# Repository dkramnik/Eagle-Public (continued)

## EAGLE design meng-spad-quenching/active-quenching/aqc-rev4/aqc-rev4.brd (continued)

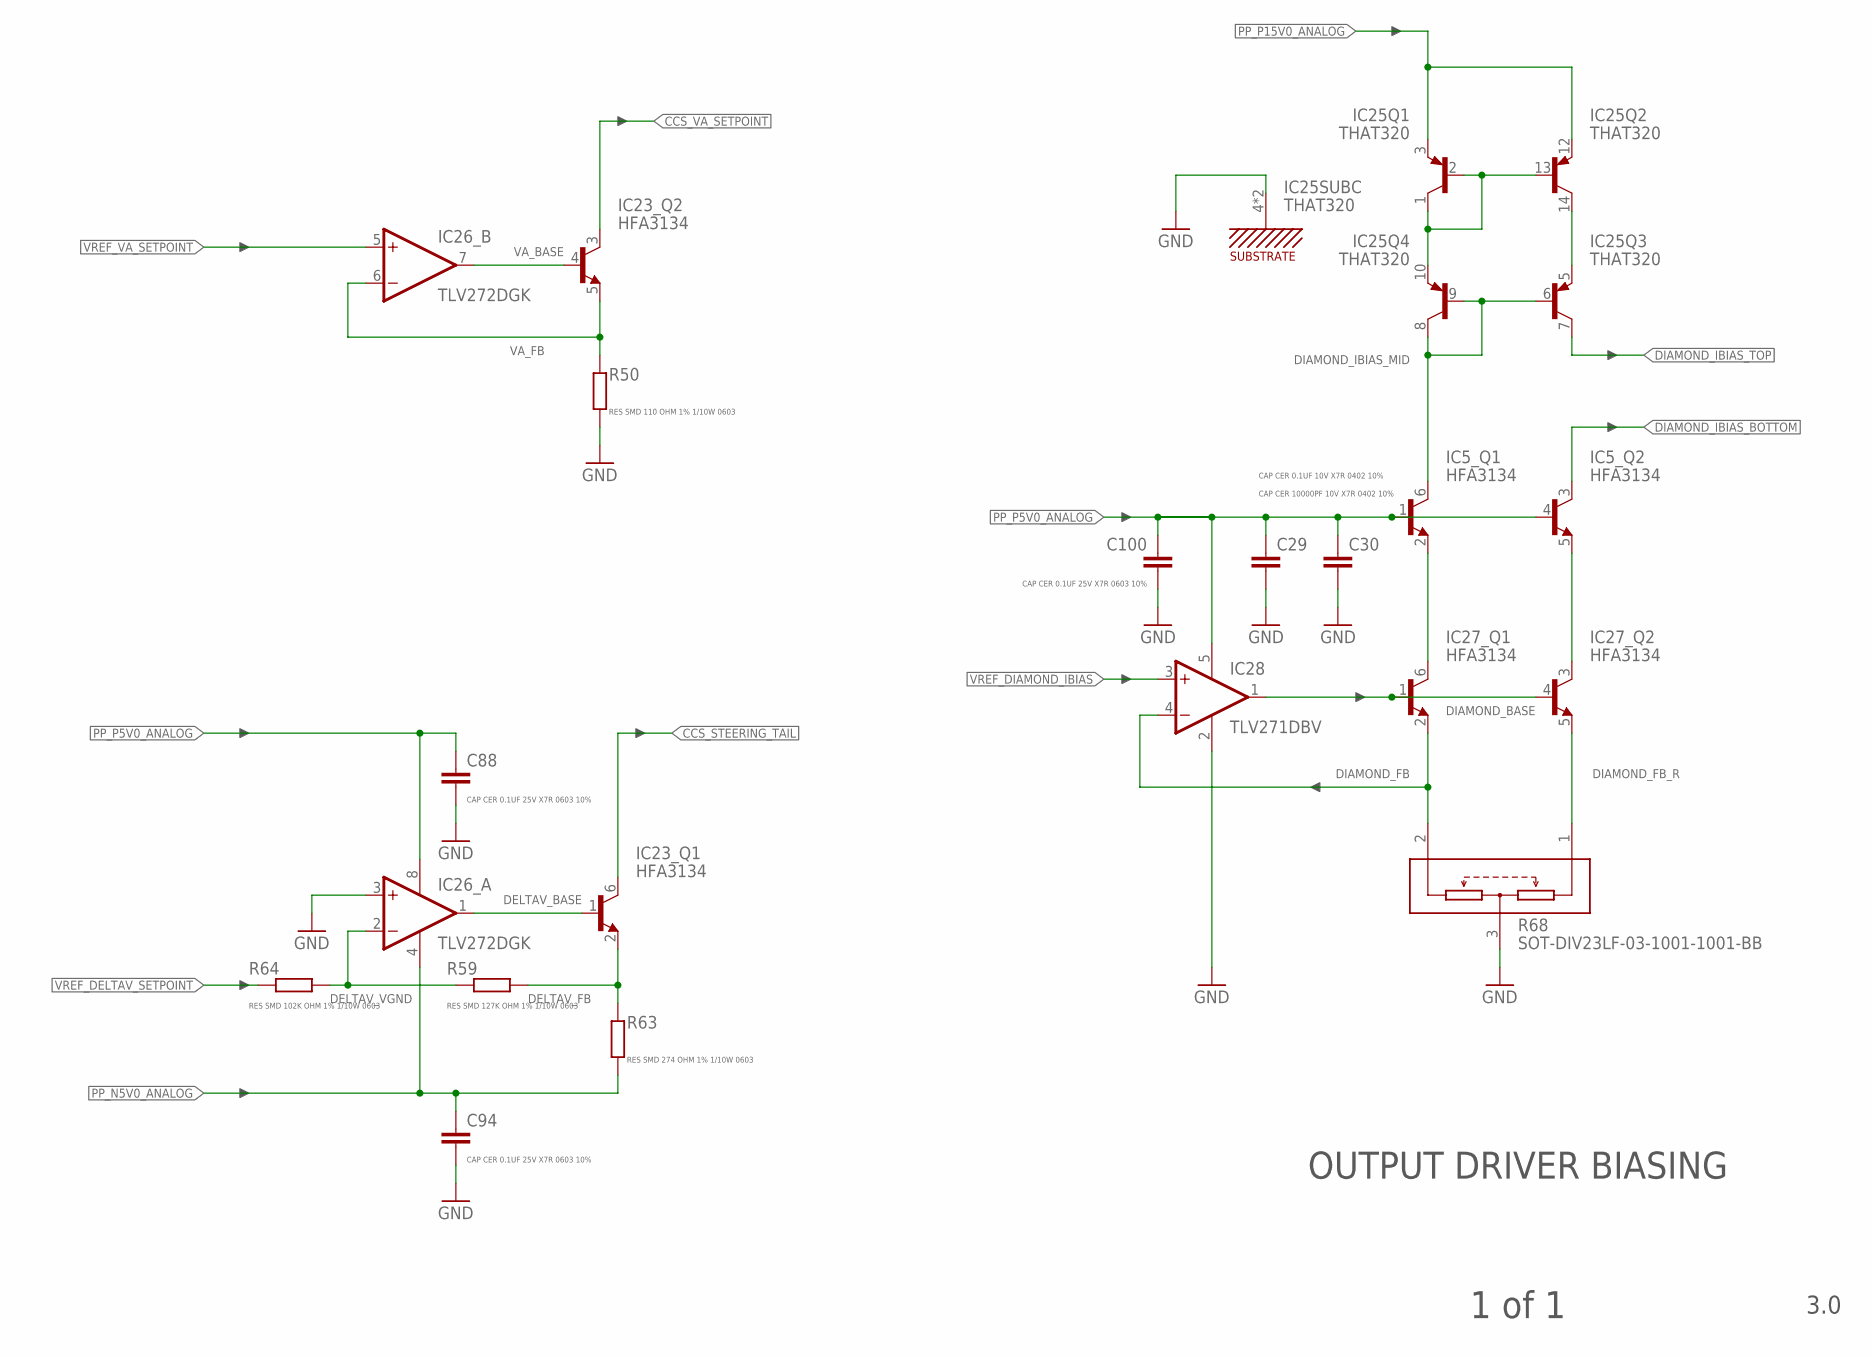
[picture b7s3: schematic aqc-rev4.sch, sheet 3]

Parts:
C29: CAP CER 0.1UF 10V X7R 0402 10%; C0402
C30: CAP CER 10000PF 10V X7R 0402 10%; C0402
C88, C94, C100: CAP CER 0.1UF 25V X7R 0603 10%; C0603
IC5, IC23, IC27: HFA3134; SOT23-6L
IC25: THAT320; SO14
IC26: TLV272DGK; MSOP8
IC28: TLV271DBV; SOT23-5
R50: RES SMD 110 OHM 1% 1/10W 0603; R0603
R59: RES SMD 127K OHM 1% 1/10W 0603; R0603
R63: RES SMD 274 OHM 1% 1/10W 0603; R0603
R64: RES SMD 102K OHM 1% 1/10W 0603; R0603
R68: SOT-DIV23LF-03-1001-1001-BB; SOT23C

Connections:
CCS_STEERING_TAIL: IC23.6 (C); also elsewhere on the board
CCS_VA_SETPOINT: IC23.3 (C); also elsewhere on the board
DELTAV_BASE: IC23.1 (B), IC26.1 (OUT)
DELTAV_FB: IC23.2 (E), R59.1, R63.2
DELTAV_VGND: IC26.2 (-IN), R59.2, R64.1
DIAMOND_BASE: IC27.1 (B), IC27.4 (B), IC28.1 (OUT)
DIAMOND_FB: IC27.2 (E), IC28.4 (-IN), R68.2 (TOP)
DIAMOND_FB_R: IC27.5 (E), R68.1 (BOTTOM)
DIAMOND_IBIAS_BOTTOM: IC5.3 (C); also elsewhere on the board
DIAMOND_IBIAS_MID: IC5.6 (C), IC25.6 (B), IC25.8 (C), IC25.9 (B)
DIAMOND_IBIAS_TOP: IC25.7 (C); also elsewhere on the board
GND: C29.2, C30.2, C88.2, C94.2, C100.2, IC25.4 (SUBC), IC25.11 (SUBC), IC26.3 (+IN), IC28.2 (V-), R50.1, R68.3 (MIDDLE); also elsewhere on the board
unnamed: IC5.2 (E), IC27.6 (C)
unnamed: IC5.5 (E), IC27.3 (C)
unnamed: IC25.1 (C), IC25.2 (B), IC25.10 (E), IC25.13 (B)
unnamed: IC25.5 (E), IC25.14 (C)
PP_N5V0_ANALOG: C94.1, IC26.4 (V-), R63.1; also elsewhere on the board
PP_P5V0_ANALOG: C29.1, C30.1, C88.1, C100.1, IC5.1 (B), IC5.4 (B), IC26.8 (V+), IC28.5 (V+); also elsewhere on the board
PP_P15V0_ANALOG: IC25.3 (E), IC25.12 (E); also elsewhere on the board
VA_BASE: IC23.4 (B), IC26.7 (OUT)
VA_FB: IC23.5 (E), IC26.6 (-IN), R50.2
VREF_DELTAV_SETPOINT: R64.2; also elsewhere on the board
VREF_DIAMOND_IBIAS: IC28.3 (+IN); also elsewhere on the board
VREF_VA_SETPOINT: IC26.5 (+IN); also elsewhere on the board

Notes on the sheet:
OUTPUT DRIVER BIASING
3.0
1 of 1

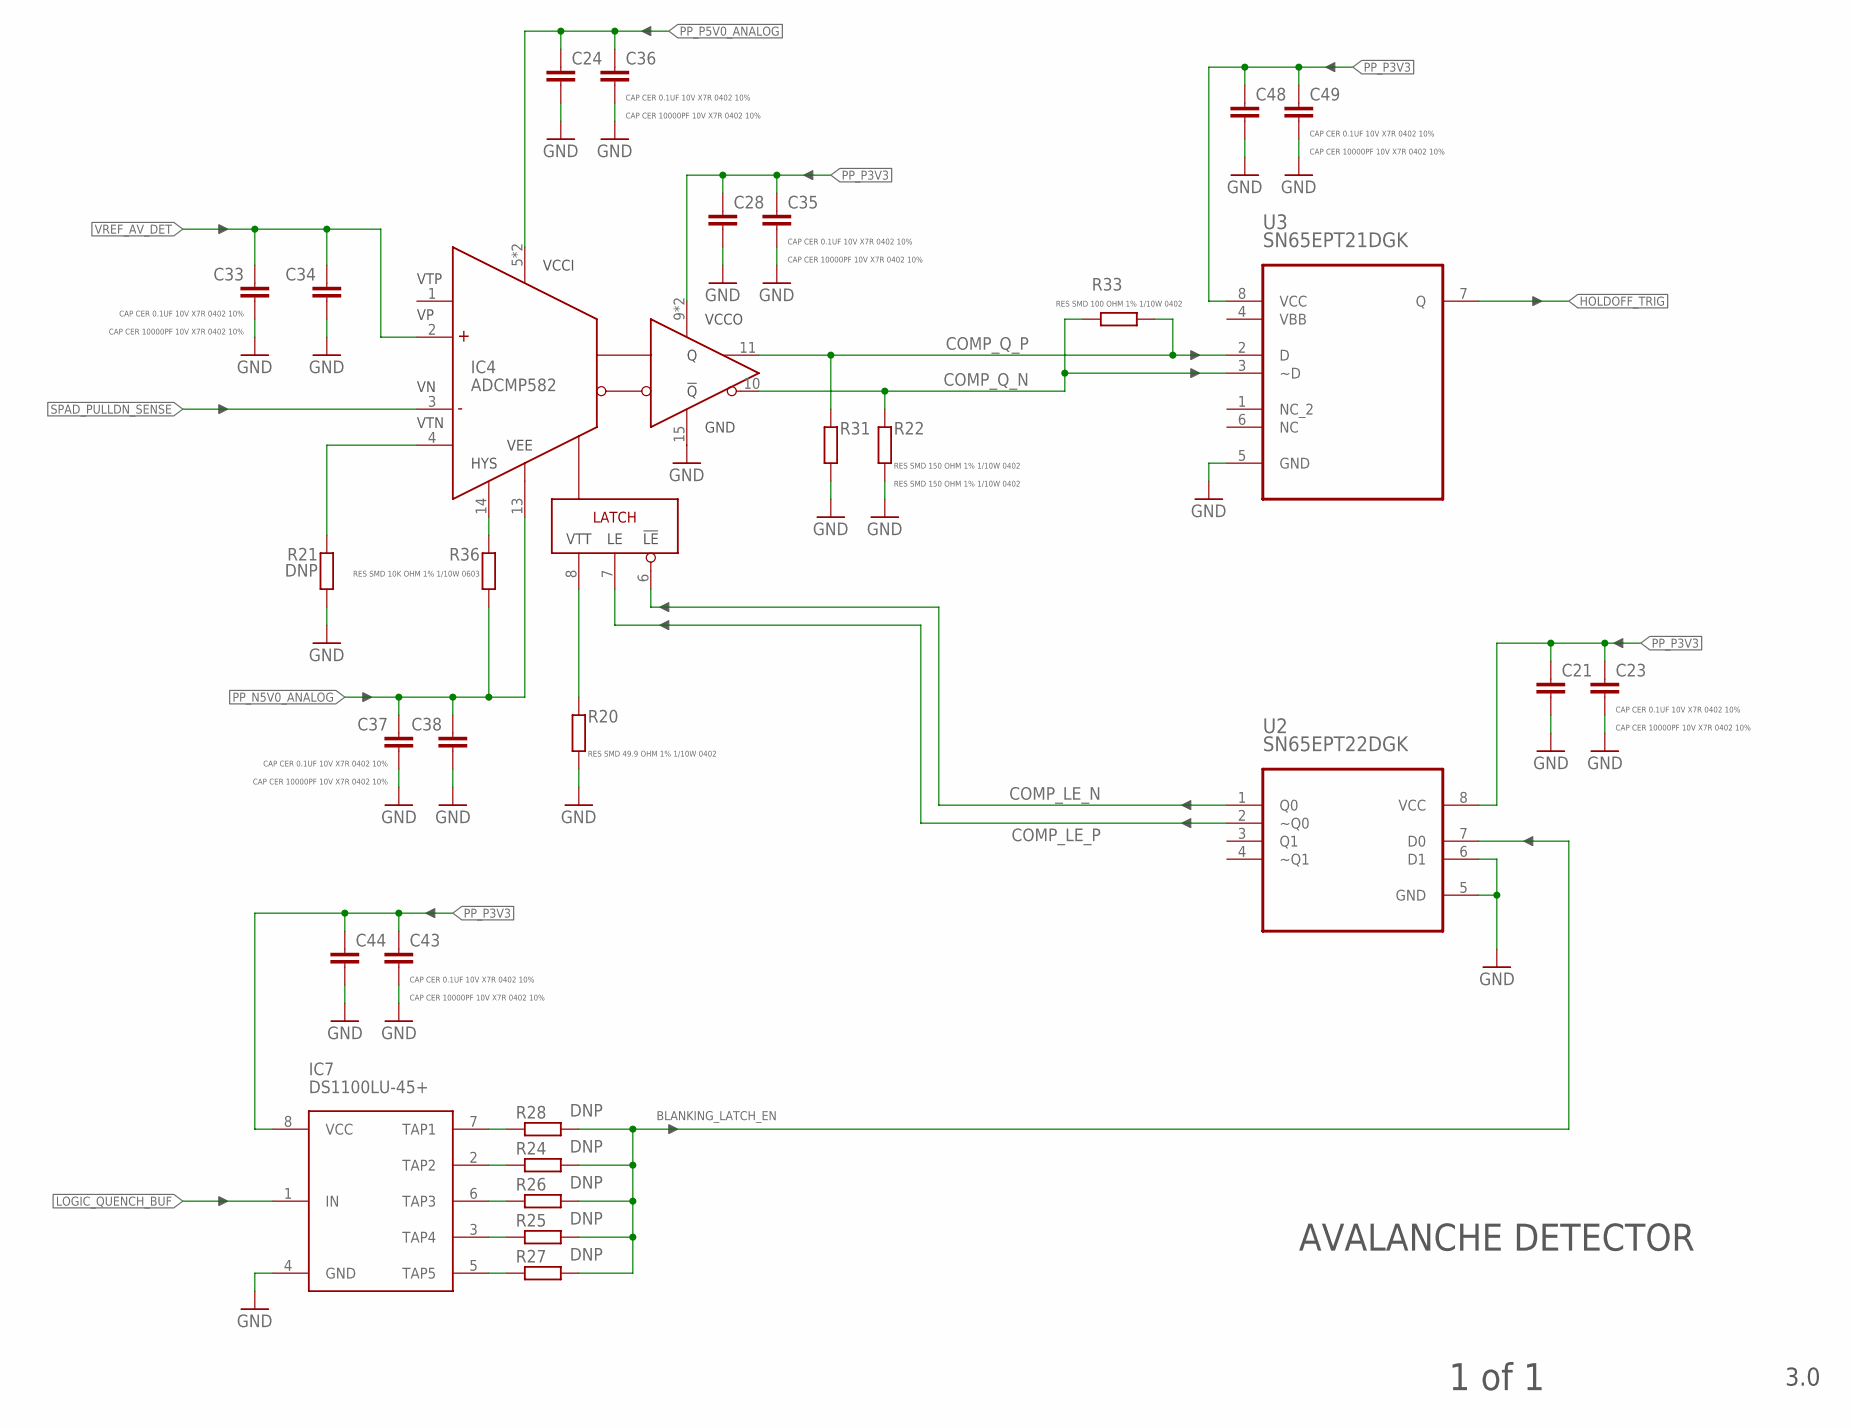
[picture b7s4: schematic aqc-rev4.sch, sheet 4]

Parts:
C21, C24, C28, C34, C38, C44, C48: CAP CER 10000PF 10V X7R 0402 10%; C0402
C23, C33, C35, C36, C37, C43, C49: CAP CER 0.1UF 10V X7R 0402 10%; C0402
IC4: ADCMP582; QFN50P300X300X80-16N
IC7: DS1100LU-45+; MSOP8
R20: RES SMD 49.9 OHM 1% 1/10W 0402; R0402
R21, R24, R25, R26, R27, R28: DNP; R0603
R22, R31: RES SMD 150 OHM 1% 1/10W 0402; R0402
R33: RES SMD 100 OHM 1% 1/10W 0402; R0402
R36: RES SMD 10K OHM 1% 1/10W 0603; R0603
U2: SN65EPT22DGK; SOP65P490X110-8N
U3: SN65EPT21DGK; SOP65P490X110-8N

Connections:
BLANKING_LATCH_EN: R24.1, R25.1, R26.1, R27.1, R28.1, U2.7 (D0)
COMP_HYS: IC4.14 (HYS), R36.2
COMP_LE_N: IC4.6 (!LE), U2.1 (Q0)
COMP_LE_P: IC4.7 (LE), U2.2 (~Q0)
COMP_Q_N: IC4.10 (!Q), R22.1, R33.1, U3.3 (~D)
COMP_Q_P: IC4.11 (Q), R31.1, R33.2, U3.2 (D)
COMP_VTN: IC4.4 (VTN), R21.2
COMP_VTT: IC4.8 (VTT), R20.1
GND: C21.2, C23.2, C24.2, C28.2, C33.2, C34.2, C35.2, C36.2, C37.2, C38.2, C43.2, C44.2, C48.2, C49.2, IC4.15 (GND), IC7.4 (GND), R20.2, R21.1, R22.2, R31.2, U2.5 (GND), U2.6 (D1), U3.5 (GND); also elsewhere on the board
HOLDOFF_TRIG: U3.7 (Q); also elsewhere on the board
LOGIC_QUENCH_BUF: IC7.1 (IN); also elsewhere on the board
PP_N5V0_ANALOG: C37.1, C38.1, IC4.13 (VEE), R36.1; also elsewhere on the board
PP_P3V3: C21.1, C23.1, C28.1, C35.1, C43.1, C44.1, C48.1, C49.1, IC4.9 (VCCO), IC4.12 (VCCO), IC7.8 (VCC), U2.8 (VCC), U3.8 (VCC); also elsewhere on the board
PP_P5V0_ANALOG: C24.1, C36.1, IC4.5 (VCCI), IC4.16 (VCCI); also elsewhere on the board
SPAD_PULLDN_SENSE: IC4.3 (VN); also elsewhere on the board
TAP1: IC7.7 (TAP1), R28.2
TAP2: IC7.2 (TAP2), R24.2
TAP3: IC7.6 (TAP3), R26.2
TAP4: IC7.3 (TAP4), R25.2
TAP5: IC7.5 (TAP5), R27.2
VBB: U3.4 (VBB)
VREF_AV_DET: C33.1, C34.1, IC4.2 (VP); also elsewhere on the board

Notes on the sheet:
AVALANCHE DETECTOR
3.0
1 of 1

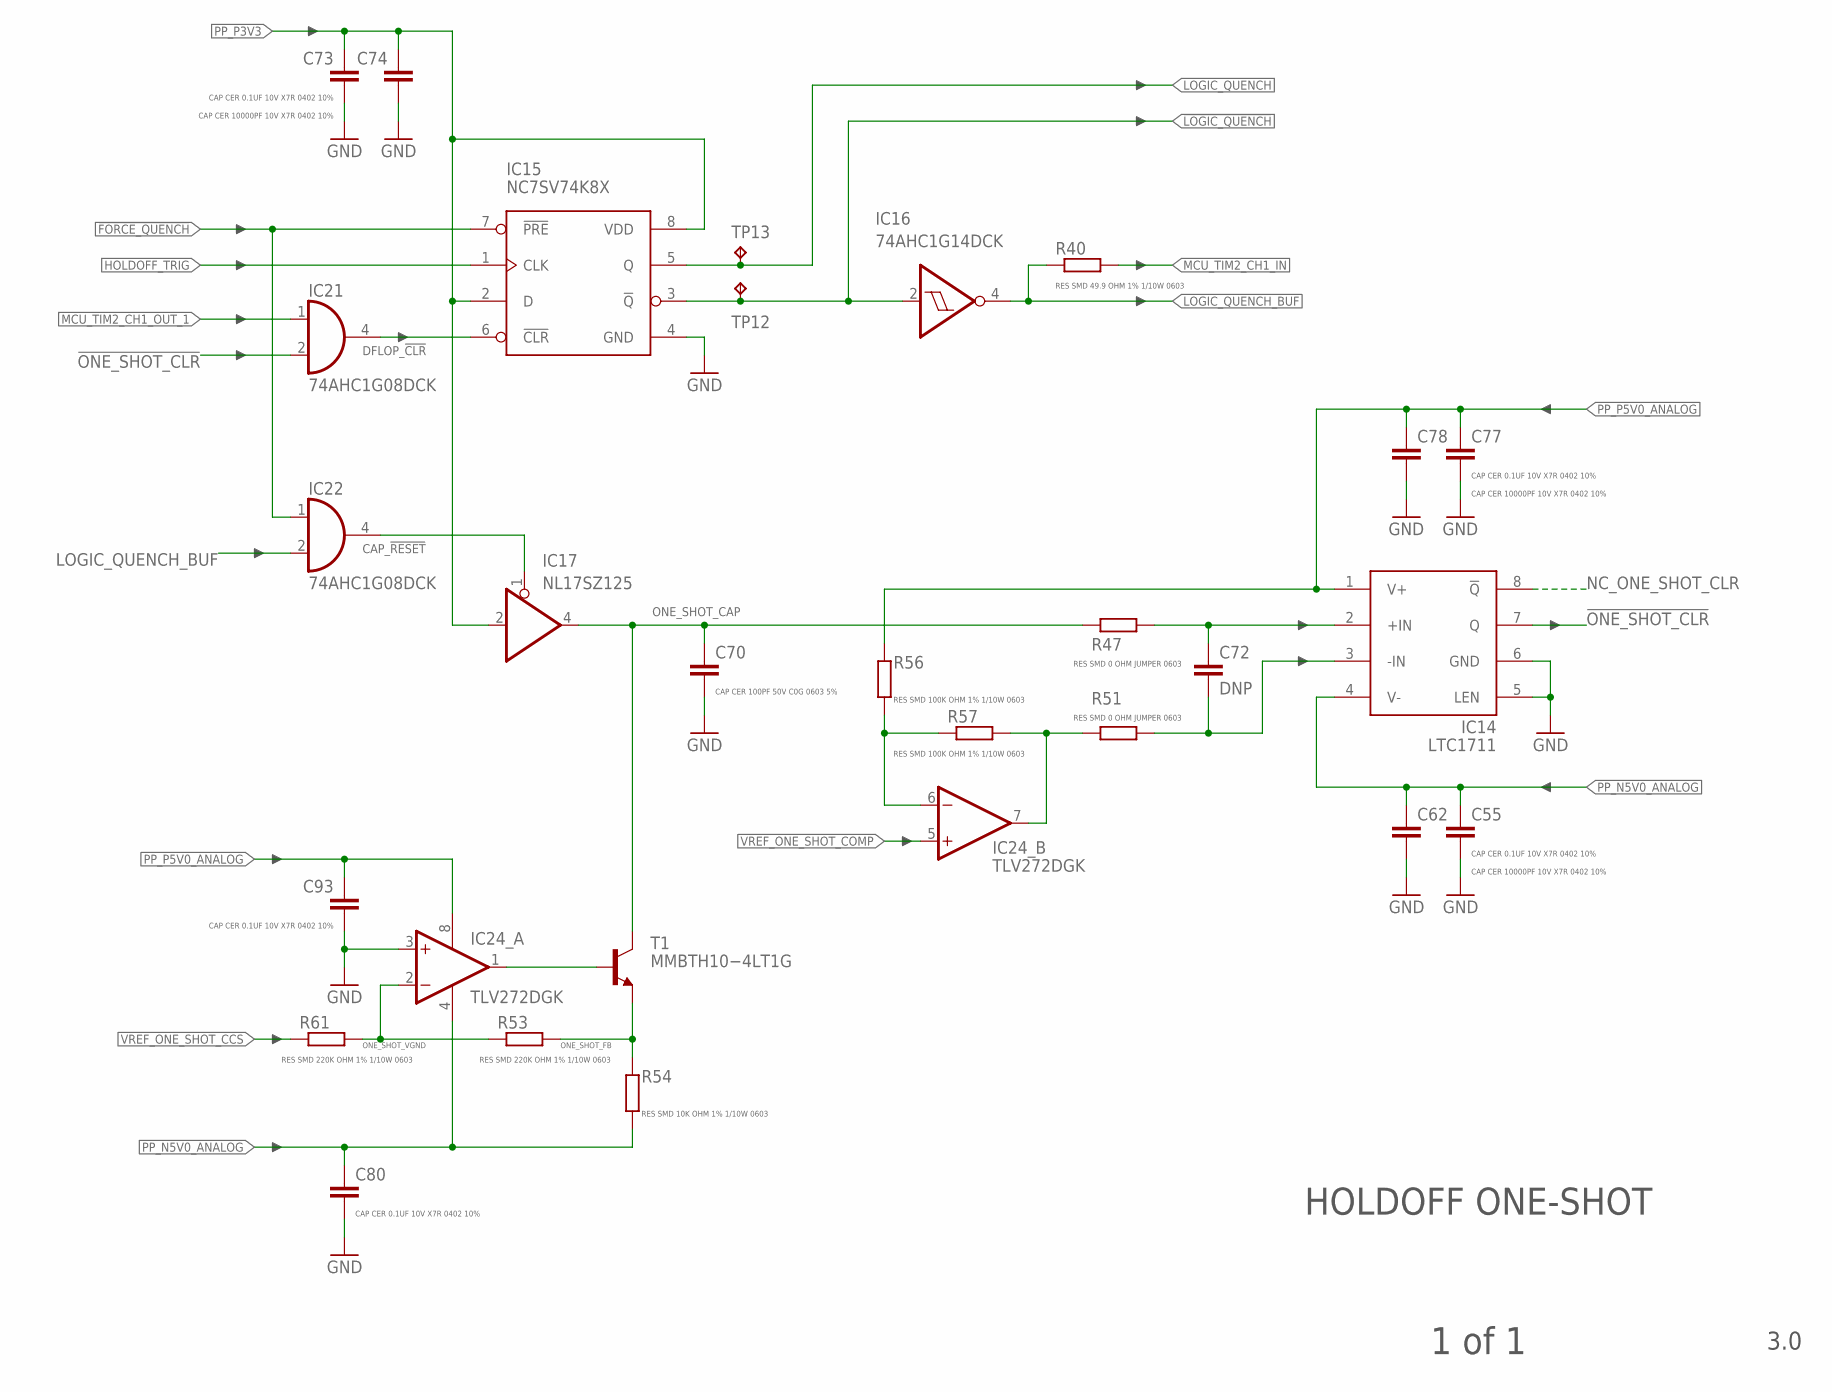
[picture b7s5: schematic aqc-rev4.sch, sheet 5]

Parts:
C55, C73, C77, C80, C93: CAP CER 0.1UF 10V X7R 0402 10%; C0402
C62, C74, C78: CAP CER 10000PF 10V X7R 0402 10%; C0402
C70: CAP CER 100PF 50V C0G 0603 5%; C0603
C72: DNP; C0402
IC14: LTC1711; MSOP8
IC15: NC7SV74K8X; US8_3.1MM_JDEC_MO-187
IC16: 74AHC1G14DCK; SC70-5
IC17: NL17SZ125; SC70-5
IC21, IC22: 74AHC1G08DCK; SC70-5
IC24: TLV272DGK; MSOP8
R40: RES SMD 49.9 OHM 1% 1/10W 0603; R0603
R47, R51: RES SMD 0 OHM JUMPER 0603; R0603
R53, R61: RES SMD 220K OHM 1% 1/10W 0603; R0603
R54: RES SMD 10K OHM 1% 1/10W 0603; R0603
R56, R57: RES SMD 100K OHM 1% 1/10W 0603; R0603
T1: MMBTH10−4LT1G; SOT23-BEC
TP12, TP13: TPTP06R; TP06R

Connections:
!FORCE_QUENCH: IC15.7 (!PRE), IC22.1 (I0); also elsewhere on the board
!LOGIC_QUENCH: IC15.3 (!Q), IC16.2 (I), TP12.TP; also elsewhere on the board
!ONE_SHOT_CLR: IC14.7 (Q), IC21.2 (I1)
CAP_!RESET: IC17.1 (OE), IC22.4 (O)
DFLOP_!CLR: IC15.6 (!CLR), IC21.4 (O)
GND: C55.2, C62.2, C70.2, C73.2, C74.2, C77.2, C78.2, C80.2, C93.2, IC14.5 (LEN), IC14.6 (GND), IC15.4 (GND), IC24.3 (+IN); also elsewhere on the board
HOLDOFF_TRIG: IC15.1 (CLK); also elsewhere on the board
LOGIC_QUENCH: IC15.5 (Q), TP13.TP; also elsewhere on the board
LOGIC_QUENCH_BUF: IC16.4 (O), IC22.2 (I1), R40.2; also elsewhere on the board
MCU_TIM2_CH1_IN: R40.1; also elsewhere on the board
MCU_TIM2_CH1_OUT_1: IC21.1 (I0); also elsewhere on the board
unnamed: IC24.1 (OUT), T1.B
unnamed: IC24.7 (OUT), R51.2, R57.1
unnamed: IC24.6 (-IN), R56.1, R57.2
unnamed: C72.2, IC14.3 (-IN), R51.1
unnamed: C72.1, IC14.2 (+IN), R47.1
NC_ONE_SHOT_CLR: IC14.8 (!Q)
ONE_SHOT_CAP: C70.1, IC17.4 (O), R47.2, T1.C
ONE_SHOT_FB: R53.1, R54.1, T1.E
ONE_SHOT_VGND: IC24.2 (-IN), R53.2, R61.1
PP_N5V0_ANALOG: C55.1, C62.1, C80.1, IC14.4 (V-), IC24.4 (V-), R54.2; also elsewhere on the board
PP_P3V3: C73.1, C74.1, IC15.2 (D), IC15.8 (VDD), IC17.2 (I); also elsewhere on the board
PP_P5V0_ANALOG: C77.1, C78.1, C93.1, IC14.1 (V+), IC24.8 (V+), R56.2; also elsewhere on the board
VREF_ONE_SHOT_CCS: R61.2; also elsewhere on the board
VREF_ONE_SHOT_COMP: IC24.5 (+IN); also elsewhere on the board

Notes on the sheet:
HOLDOFF ONE-SHOT
3.0
1 of 1

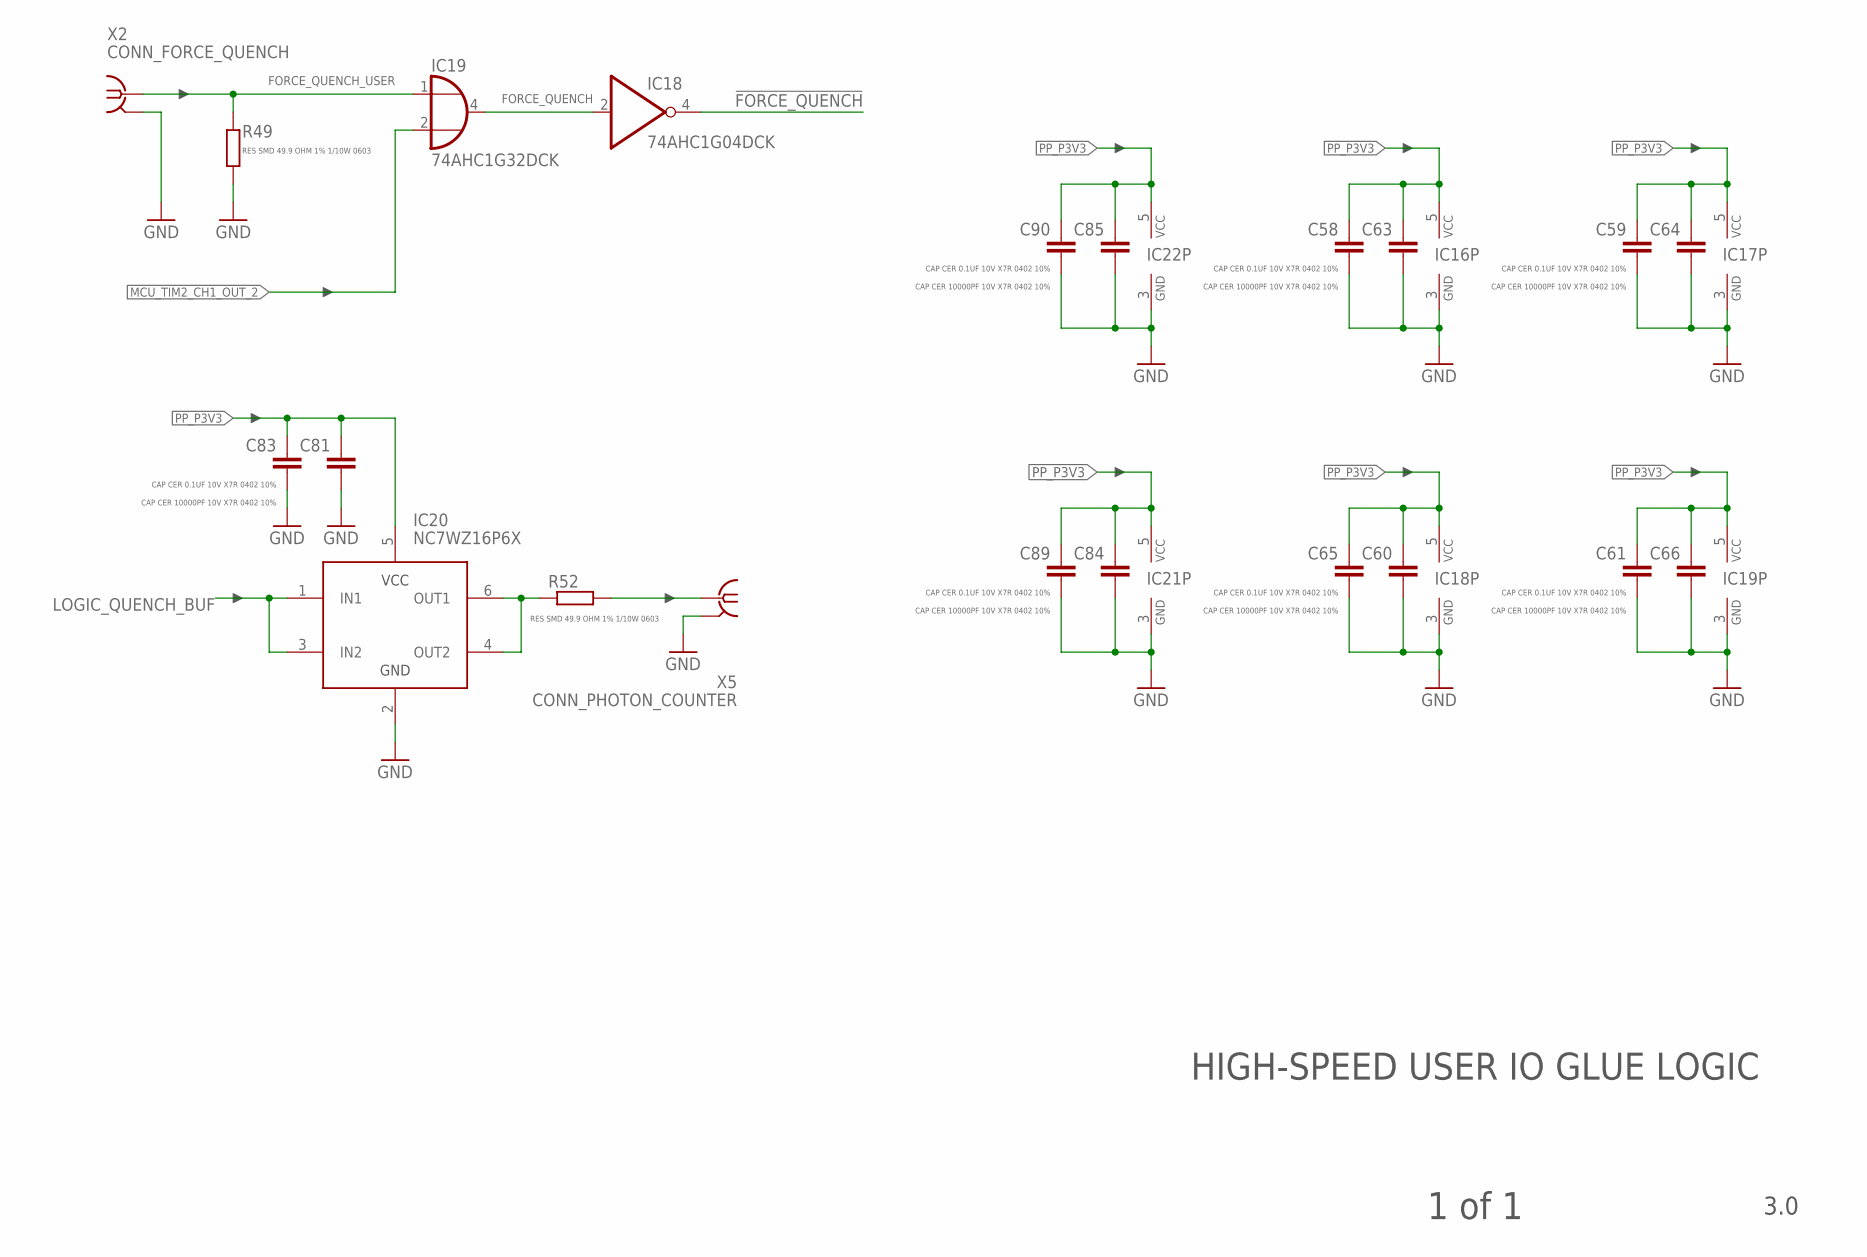
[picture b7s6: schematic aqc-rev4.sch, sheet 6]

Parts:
C58, C59, C61, C65, C83, C89, C90: CAP CER 0.1UF 10V X7R 0402 10%; C0402
C60, C63, C64, C66, C81, C84, C85: CAP CER 10000PF 10V X7R 0402 10%; C0402
IC16: 74AHC1G14DCK; SC70-5
IC17: NL17SZ125; SC70-5
IC18: 74AHC1G04DCK; SC70-5
IC19: 74AHC1G32DCK; SC70-5
IC20: NC7WZ16P6X; SC70-6L
IC21, IC22: 74AHC1G08DCK; SC70-5
R49, R52: RES SMD 49.9 OHM 1% 1/10W 0603; R0603
X2: CONN_FORCE_QUENCH; J502-ND-142-0701-881/886; MPN 142-0711-871
X5: CONN_PHOTON_COUNTER; J502-ND-142-0701-881/886

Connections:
!FORCE_QUENCH: IC18.4 (O); also elsewhere on the board
FORCE_QUENCH: IC18.2 (I), IC19.4 (O)
FORCE_QUENCH_USER: IC19.1 (I0), R49.2, X2.1
GND: C58.2, C59.2, C60.2, C61.2, C63.2, C64.2, C65.2, C66.2, C81.2, C83.2, C84.2, C85.2, C89.2, C90.2, IC16.3 (GND), IC17.3 (GND), IC18.3 (GND), IC19.3 (GND), IC20.2 (GND), IC21.3 (GND), IC22.3 (GND), R49.1, X2.G@1 (GND), X2.G@2 (GND), X2.G@3 (GND), X2.G@4 (GND), X5.G@1 (GND), X5.G@2 (GND), X5.G@3 (GND), X5.G@4 (GND); also elsewhere on the board
LOGIC_QUENCH_BUF: IC20.1 (IN1), IC20.3 (IN2); also elsewhere on the board
MCU_TIM2_CH1_OUT_2: IC19.2 (I1); also elsewhere on the board
unnamed: IC20.4 (OUT2), IC20.6 (OUT1), R52.2
PHOTON_COUNT_OUT: R52.1, X5.1
PP_P3V3: C58.1, C59.1, C60.1, C61.1, C63.1, C64.1, C65.1, C66.1, C81.1, C83.1, C84.1, C85.1, C89.1, C90.1, IC16.5 (VCC), IC17.5 (VCC), IC18.5 (VCC), IC19.5 (VCC), IC20.5 (VCC), IC21.5 (VCC), IC22.5 (VCC); also elsewhere on the board

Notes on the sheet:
HIGH-SPEED USER IO GLUE LOGIC
3.0
1 of 1

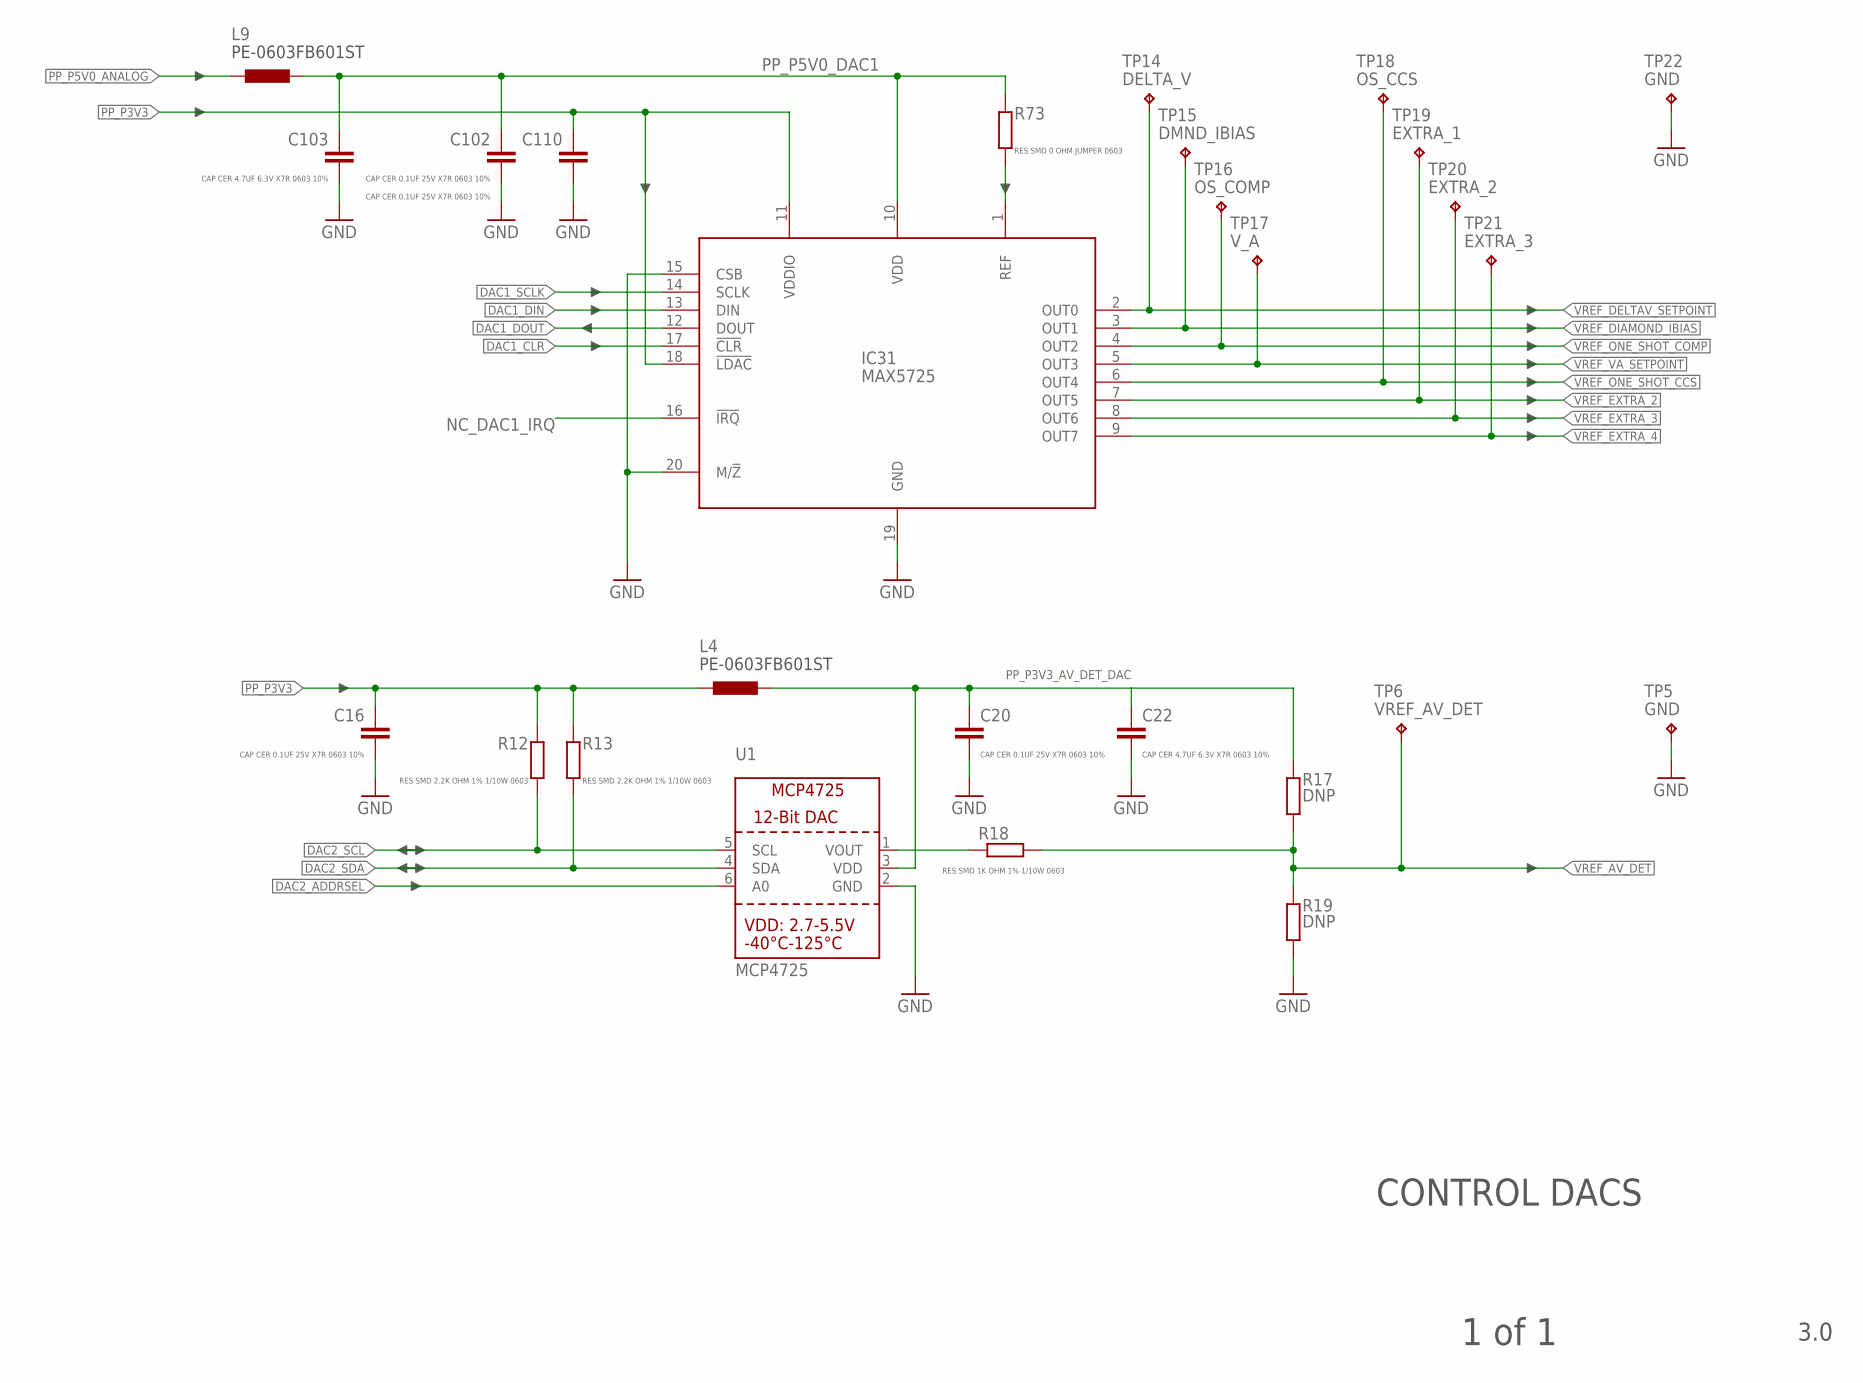
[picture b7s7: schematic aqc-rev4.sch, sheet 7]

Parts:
C16, C20, C102, C110: CAP CER 0.1UF 25V X7R 0603 10%; C0603
C22, C103: CAP CER 4.7UF 6.3V X7R 0603 10%; C0603
IC31: MAX5725; TSSOP20
L4, L9: PE-0603FB601ST; R0603
R12, R13: RES SMD 2.2K OHM 1% 1/10W 0603; R0603
R17, R19: DNP; R0603
R18: RES SMD 1K OHM 1% 1/10W 0603; R0603
R73: RES SMD 0 OHM JUMPER 0603; R0603
TP5, TP22: GND; KEYSTONE_5000_MINIATURE
TP6: VREF_AV_DET; KEYSTONE_5000_MINIATURE
TP14: DELTA_V; KEYSTONE_5000_MINIATURE
TP15: DMND_IBIAS; KEYSTONE_5000_MINIATURE
TP16: OS_COMP; KEYSTONE_5000_MINIATURE
TP17: V_A; KEYSTONE_5000_MINIATURE
TP18: OS_CCS; KEYSTONE_5000_MINIATURE
TP19: EXTRA_1; KEYSTONE_5000_MINIATURE
TP20: EXTRA_2; KEYSTONE_5000_MINIATURE
TP21: EXTRA_3; KEYSTONE_5000_MINIATURE
U1: MCP4725; SOT23-6

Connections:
DAC1_!CLR: IC31.17 (!CLR); also elsewhere on the board
DAC1_DIN: IC31.13 (DIN); also elsewhere on the board
DAC1_DOUT: IC31.12 (DOUT); also elsewhere on the board
DAC1_SCLK: IC31.14 (SCLK); also elsewhere on the board
DAC2_ADDRSEL: U1.6 (A0); also elsewhere on the board
DAC2_SCL: R12.2, U1.5 (SCL); also elsewhere on the board
DAC2_SDA: R13.2, U1.4 (SDA); also elsewhere on the board
GND: C16.2, C20.2, C22.2, C102.2, C103.2, C110.2, IC31.15 (CSB), IC31.19 (GND), IC31.20 (M/!Z), R19.1, TP5.P$1, TP22.P$1, U1.2 (GND); also elsewhere on the board
unnamed: R18.2, U1.1 (VOUT)
unnamed: IC31.1 (REF), R73.2
NC_DAC1_IRQ: IC31.16 (!IRQ)
PP_P3V3: C16.1, C110.1, IC31.11 (VDDIO), IC31.18 (!LDAC), L4.1, R12.1, R13.1; also elsewhere on the board
PP_P3V3_AV_DET_DAC: C20.1, C22.1, L4.2, R17.2, U1.3 (VDD)
PP_P5V0_ANALOG: L9.1; also elsewhere on the board
PP_P5V0_DAC1: C102.1, C103.1, IC31.10 (VDD), L9.2, R73.1
VREF_AV_DET: R17.1, R18.1, R19.2, TP6.P$1; also elsewhere on the board
VREF_DELTAV_SETPOINT: IC31.2 (OUT0), TP14.P$1; also elsewhere on the board
VREF_DIAMOND_IBIAS: IC31.3 (OUT1), TP15.P$1; also elsewhere on the board
VREF_EXTRA_2: IC31.7 (OUT5), TP19.P$1
VREF_EXTRA_3: IC31.8 (OUT6), TP20.P$1
VREF_EXTRA_4: IC31.9 (OUT7), TP21.P$1
VREF_ONE_SHOT_CCS: IC31.6 (OUT4), TP18.P$1; also elsewhere on the board
VREF_ONE_SHOT_COMP: IC31.4 (OUT2), TP16.P$1; also elsewhere on the board
VREF_VA_SETPOINT: IC31.5 (OUT3), TP17.P$1; also elsewhere on the board

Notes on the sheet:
CONTROL DACS
3.0
1 of 1

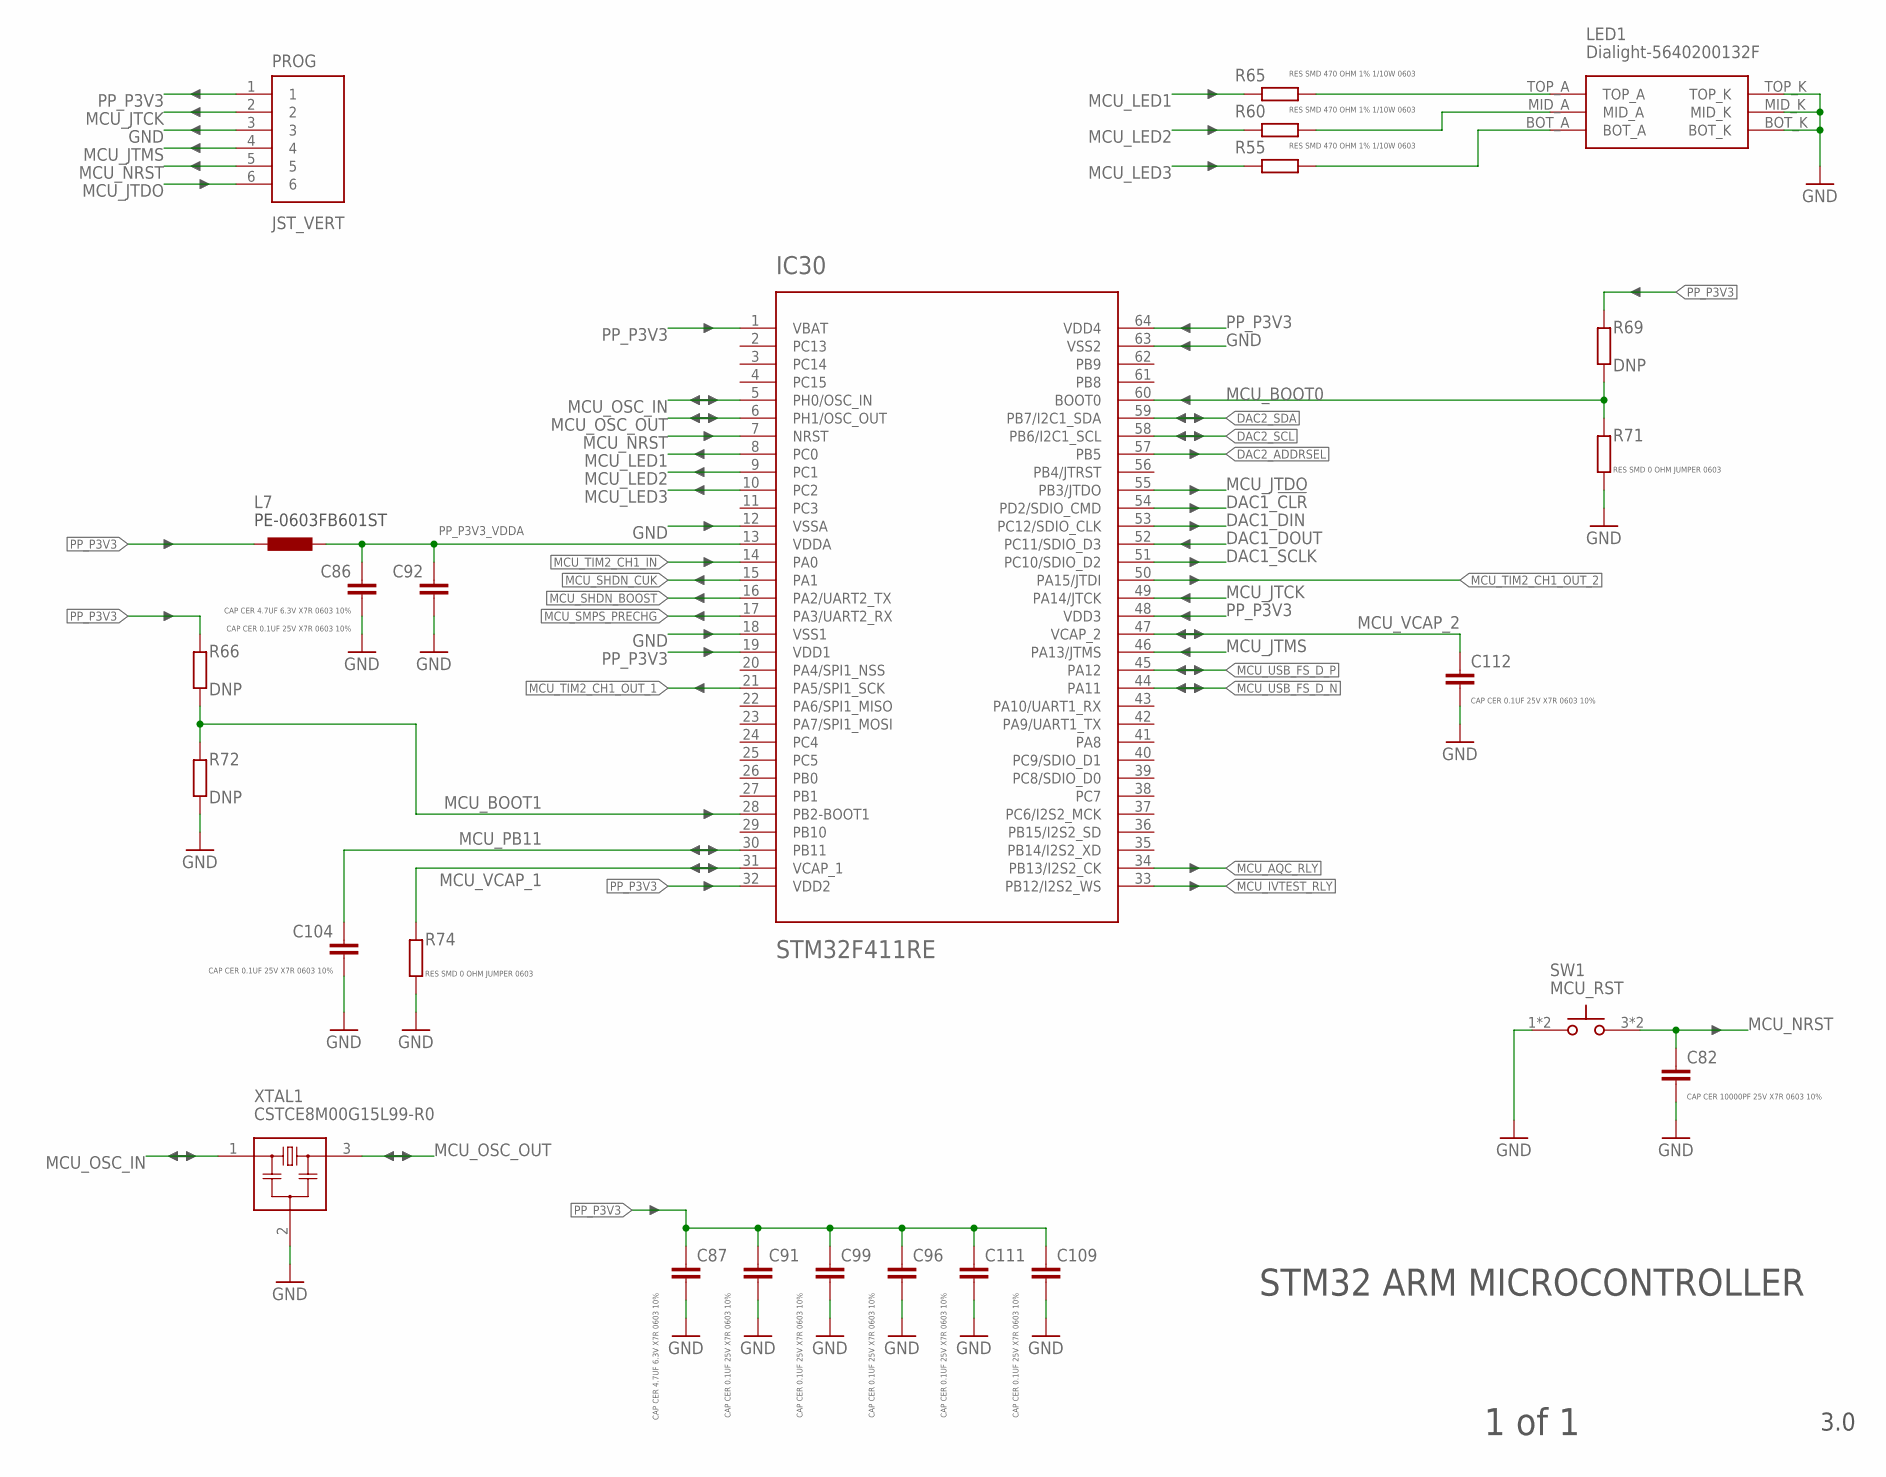
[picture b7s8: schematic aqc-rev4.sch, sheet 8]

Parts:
C82: CAP CER 10000PF 25V X7R 0603 10%; C0603
C86, C87: CAP CER 4.7UF 6.3V X7R 0603 10%; C0603
C91, C92, C96, C99, C104, C109, C111, C112: CAP CER 0.1UF 25V X7R 0603 10%; C0603
IC30: STM32F411RE; TQFP64_STM32
L7: PE-0603FB601ST; R0603
LED1: Dialight-5640200132F; CBI-564-0X00-XXX
PROG: JST_VERT; JST-6-SMD-VERT-1.0MM
R55, R60, R65: RES SMD 470 OHM 1% 1/10W 0603; R0603
R66, R69, R72: DNP; R0603
R71, R74: RES SMD 0 OHM JUMPER 0603; R0603
SW1: MCU_RST; E-SWITCH-TL3305AF160QG
XTAL1: CSTCE8M00G15L99-R0; CSTCE_G15L/CSTCE_GH5L

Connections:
!MCU_SHDN_BOOST: IC30.16 (PA2/UART2_TX); also elsewhere on the board
!MCU_SHDN_CUK: IC30.15 (PA1); also elsewhere on the board
!MCU_SMPS_PRECHG: IC30.17 (PA3/UART2_RX); also elsewhere on the board
DAC1_!CLR: IC30.54 (PD2/SDIO_CMD); also elsewhere on the board
DAC1_DIN: IC30.53 (PC12/SDIO_CLK); also elsewhere on the board
DAC1_DOUT: IC30.52 (PC11/SDIO_D3); also elsewhere on the board
DAC1_SCLK: IC30.51 (PC10/SDIO_D2); also elsewhere on the board
DAC2_ADDRSEL: IC30.57 (PB5); also elsewhere on the board
DAC2_SCL: IC30.58 (PB6/I2C1_SCL); also elsewhere on the board
DAC2_SDA: IC30.59 (PB7/I2C1_SDA); also elsewhere on the board
GND: C82.2, C86.2, C87.2, C91.2, C92.2, C96.2, C99.2, C104.2, C109.2, C111.2, C112.2, IC30.12 (VSSA), IC30.18 (VSS1), IC30.63 (VSS2), LED1.BOT_K, LED1.MID_K, LED1.TOP_K, PROG.3, R71.2, R72.2, R74.2, SW1.1, SW1.2, XTAL1.2 (GND); also elsewhere on the board
MCU_AQC_RLY: IC30.34 (PB13/I2S2_CK); also elsewhere on the board
MCU_BOOT0: IC30.60 (BOOT0), R69.2, R71.1
MCU_BOOT1: IC30.28 (PB2-BOOT1), R66.2, R72.1
MCU_IVTEST_RLY: IC30.33 (PB12/I2S2_WS); also elsewhere on the board
MCU_JTCK: IC30.49 (PA14/JTCK), PROG.2
MCU_JTDO: IC30.55 (PB3/JTDO), PROG.6
MCU_JTMS: IC30.46 (PA13/JTMS), PROG.4
MCU_LED1: IC30.8 (PC0), R65.2
MCU_LED2: IC30.9 (PC1), R60.2
MCU_LED3: IC30.10 (PC2), R55.2
MCU_NRST: C82.1, IC30.7 (NRST), PROG.5, SW1.3, SW1.4
MCU_OSC_IN: IC30.5 (PH0/OSC_IN), XTAL1.1 (LEFT)
MCU_OSC_OUT: IC30.6 (PH1/OSC_OUT), XTAL1.3 (RIGHT)
MCU_PB11: C104.1, IC30.30 (PB11)
MCU_TIM2_CH1_IN: IC30.14 (PA0); also elsewhere on the board
MCU_TIM2_CH1_OUT_1: IC30.21 (PA5/SPI1_SCK); also elsewhere on the board
MCU_TIM2_CH1_OUT_2: IC30.50 (PA15/JTDI); also elsewhere on the board
MCU_USB_FS_D_N: IC30.44 (PA11); also elsewhere on the board
MCU_USB_FS_D_P: IC30.45 (PA12); also elsewhere on the board
MCU_VCAP_1: IC30.31 (VCAP_1), R74.1
MCU_VCAP_2: C112.1, IC30.47 (VCAP_2)
unnamed: LED1.TOP_A, R65.1
unnamed: LED1.MID_A, R60.1
unnamed: LED1.BOT_A, R55.1
PP_P3V3: C87.1, C91.1, C96.1, C99.1, C109.1, C111.1, IC30.1 (VBAT), IC30.19 (VDD1), IC30.32 (VDD2), IC30.48 (VDD3), IC30.64 (VDD4), L7.1, PROG.1, R66.1, R69.1; also elsewhere on the board
PP_P3V3_VDDA: C86.1, C92.1, IC30.13 (VDDA), L7.2

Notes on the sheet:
STM32 ARM MICROCONTROLLER
3.0
1 of 1
